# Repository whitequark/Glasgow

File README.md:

# Glasgow Debug Tool

**Want one? The [Crowdsupply campaign](https://www.crowdsupply.com/1bitsquared/glasgow) is now live.**

**Let's chat! Our IRC channel is [#glasgow at libera.chat](irc://irc.libera.chat/glasgow); our Discord channel is [#glasgow at 1BitSquared's Discord server](https://1bitsquared.com/pages/chat).**

**Important note: if you are looking to assemble boards yourself, use only revC1.**

## What is Glasgow?

Glasgow is a tool for exploring digital interfaces, aimed at embedded developers, reverse engineers, digital archivists, electronics hobbyists, and everyone else who wants to communicate to a wide selection of digital devices with high reliability and minimum hassle. It can be attached to most devices without additional active or passive components, and includes extensive protection from unexpected conditions and operator error.

The Glasgow hardware can support many digital interfaces because it uses reconfigurable logic. Instead of only offering a small selection of standard hardware supported interfaces, it uses an FPGA to adapt on the fly to the task at hand without compromising on performance or reliability, even for unusual, custom or obsolete interfaces.

The Glasgow software is a set of building blocks designed to eliminate incidental complexity. Each interface is packaged into a self-contained *applet* that can be used directly from the command line, or reused as a part of a more complex system. Using Glasgow does not require any programming knowledge, although it becomes much more powerful if you know a bit of Python.

## What can I do with Glasgow?

Some of the tasks Glasgow can do well are:

  * communicate via UART,
    * automatically determine and follow the baud rate of device under test,
  * initiate transactions via SPI or I²C,
  * read and write 24-series I²C EEPROMs,
  * read and write 25-series SPI Flash memories,
    * determine memory parameters via SFDP,
  * read and write ONFI-compatible Flash memories,
    * determine memory parameters via ONFI parameter page,
  * read and write parallel 27/28/29-series EPROMs, EEPROMs and Flash memories,
    * determine the extent of floating gate charge decay and rescue data,
  * program and verify AVR microcontrollers with SPI interface,
  * automatically determine unknown JTAG pinout,
  * play back JTAG SVF files,
  * debug ARC processors via JTAG,
  * debug some MIPS processors via EJTAG,
  * program and verify XC9500XL CPLDs via JTAG,
  * communicate using nRF24L01(+) radios,
  * program nRF24LE1 and nRF24LU1(+) microcontrollers,
  * synthesize sound using a Yamaha OPLx/OPM chip and play it in real time on a webpage,
  * read raw modulated data from 5.25"/3.5" floppy drives,
  * ... and more!

Everything above can be done with only a Glasgow revC board, some wires, and depending on the device under test, external power.

## How does using Glasgow look like?

Watch a typical command-line workflow in this screencast:

## What hardware does Glasgow use?

The Glasgow hardware evolves over time, with each major milestone called a "revision". Although all revisions are, and will always be supported with the same software, they vary significantly in their capabilities, and the chosen revision will limit the possible tasks.

Glasgow boards use a version in the `revXN` format, where `X` is a revision letter (increased on major design changes) and `N` is a stepping number (increased on any layout or component changes). For example, `revC0` is the first stepping of revision C.

### revA/revB

Revisions A and B have not been produced in significant amounts, contain major design issues, and are therefore mostly of historical interest. Nevertheless, everyone who has one of the revA/revB boards can keep using them—forever.

### revC

Revision C is the latest revision and is being prepared for mass production. It provides 16 I/O pins with a data rate up to approx. 100 Mbps/pin (50 MHz)\*, independent direction control and independent programmable pull-up/pull-down resistors. The I/O pins are grouped into two I/O ports, each of which can use any voltage from 1.8 V to 5 V, sense and monitor I/O voltage of the device under test, as well as provide up to 150 mA of power. The board uses USB 2 for power, configuration, and communication, achieving up to 336 Mbps (42 MB/s) of sustained combined throughput.

<sub>\* Data rate achievable in practice depends on many factors and will vary greatly with specific interface and applet design. 12 Mbps/pin (6 MHz) can be achieved with minimal development effort; reaching higher data rates requires careful HDL coding and a good understanding of timing analysis.</sub>

## What software does Glasgow use?

Glasgow is written entirely in Python 3. The interface logic that runs on the FPGA is described using [nMigen](https://github.com/nmigen/nmigen/), which is a Python-based domain specific language. The supporting code that runs on the host PC is written in Python with [asyncio](https://docs.python.org/3/library/asyncio.html). This way, the logic on the FPGA can be assembled on demand for any requested configuration, keeping it as fast and compact as possible, and code can be shared between gateware and software, removing the need to add error-prone "glue" boilerplate.

Glasgow would not be possible without the [open-source iCE40 FPGA toolchain](http://www.clifford.at/icestorm/), which is not only very reliable but also extremely fast. It is so fast that FPGA bitstreams are not cached (beyond not rebuilding the bitstream already on the device), as it only takes a few seconds to build one from scratch for something like an UART. When developing a new applet it is rarely necessary to wait for the toolchain.

Implementing reliable, high-performance USB communication is not trivial—packetization, buffering, and USB quirks add up. Glasgow abstracts away USB: on the FPGA, the applet gateware writes to or reads from a FIFO, and on the host, applet software writes to or reads from a socket-like interface. Idiomatic Python code can communicate at maximum USB 2 bulk bandwidth on a modern PC without additional effort. Moreover, when a future Glasgow revision will use Ethernet in addition to USB, no changes to applet code will be required.

Debugging new applets can be hard, especially if bidirectional buses are involved. Glasgow provides a built-in cycle-accurate logic analyzer that can relate the I/O pin level and direction changes to commands and responses received and sent by the applet. The logic analyzer compresses waveforms and can pause the applet if its buffer is about to overflow.

## How do I set up Glasgow?

**If these instructions don't work for you, please [file it as a bug](https://github.com/GlasgowEmbedded/glasgow/issues), so that the experience can be made more smooth for everyone.**

### ... with Linux?

You will need git and Python 3.7 (or a newer version, in which case replace `3.7` with that version below). On a Debian or Ubuntu system these can be installed with:

    apt-get install --no-install-recommends git python3.7 python3-setuptools \
      python3-libusb1 python3-aiohttp python3-bitarray python3-crcmod

You will also need Yosys and nextpnr-ice40, both from the master branch. Follow the setup instructions for [Yosys](https://github.com/yosysHQ/yosys/#setup) and [nextpnr](https://github.com/YosysHQ/nextpnr/#nextpnr-ice40).

Obtain the source code:

    git clone https://github.com/GlasgowEmbedded/glasgow
    cd glasgow

Configure your system to allow unprivileged access (for anyone in the `plugdev` group) to the Glasgow hardware:

    sudo cp config/99-glasgow.rules /etc/udev/rules.d

Install the dependencies and the scripts for the current user:

    cd software
    python3.7 setup.py develop --user

The scripts are placed in `$HOME/.local/bin`, so be sure to add that directory to the `PATH` environment variable; after this, you can run `glasgow` from a terminal. Instead of adjusting `PATH` it is also possible to use `python3.7 -m glasgow.cli`.

To update the source code, do:

    cd glasgow
    git pull

### ... with macOS?

If you haven't already, install [Homebrew](https://brew.sh/). Now:

    brew install python
    brew tap ktemkin/oss-fpga
    brew install --HEAD icestorm yosys nextpnr-ice40

Obtain the source code:

    git clone https://github.com/GlasgowEmbedded/glasgow
    cd glasgow

Install the dependencies and the scripts for the current user:

    cd software
    python3 setup.py develop

The scripts will be installed in `/usr/local/bin`, which should already be in your `PATH`.

### ... with Windows?

Although first-class Windows support is an important goal and Glasgow already works on Windows, the installation process is not yet ready.

## How do I use Glasgow?

*Note:* if you've just assembled a new board, you'll need to follow the [factory flashing](./docs/internals_flashing.rst) instructions first.

Once you've installed the Glasgow CLI, we can run a few commands to check that it's working. First, plug in your board and check if the CLI can talk to it:

    glasgow voltage

This should display the configured and sensed voltages on Glasgow's IO ports.

Next, we can try running an applet. Here, we'll use the [uart](./software/glasgow/applet/interface/uart) applet to create a 3.3V serial port on pins 0 and 1:

    glasgow run uart -V3.3 tty

If you receive any errors when running this command, it means your FPGA toolchain (yosys/nextpnr) is not working. If it is working, you should see:

    I: g.applet.interface.uart: running on a TTY; enter `Ctrl+\ q` to quit

You'll also see the `VIO` LEDs light up on your Glasgow board to indicate there is now voltage present on the ports.

If your serial port isn't connected to anything, you'll also see some harmless `frame or parity errors detected` warnings. As the message says, you'll need to use `Ctrl+\ q` to exit the applet.

If all this succeeded, your Glasgow is working!

## Who made Glasgow?

  * [@whitequark](https://github.com/whitequark) came up with the design, coordinates the project and implements most of gateware and software;
  * [@awygle](https://github.com/awygle) designed the power/analog port circuitry and helped with layout of revB;
  * [@marcan](https://github.com/marcan) improved almost every aspect of hardware for revC;
  * [@esden](https://github.com/esden) is handling batch manufacturing;
  * [@smunaut](https://github.com/smunaut) provided advice crucial for stability and performance of USB communication;
  * [@electronic_eel](https://github.com/electronic_eel) improved the hardware for revC2, designed the test jig and is working on advanced protection circuitry;
  * [@Attie](https://github.com/attie) improved and refactored many applets;
  * ... and many [other people](https://github.com/GlasgowEmbedded/Glasgow/graphs/contributors).

## License

Glasgow is distributed under the terms of both 0-clause BSD license as well as Apache 2.0 license.

See [LICENSE-0BSD](LICENSE-0BSD.txt) and [LICENSE-Apache-2.0.txt](LICENSE-Apache-2.0.txt) for details.

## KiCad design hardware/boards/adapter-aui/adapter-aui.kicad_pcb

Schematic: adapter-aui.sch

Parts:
C1, C2, C9: 1u; C_0603_1608Metric_Pad1.05x0.95mm_HandSolder
C3, C4: 100n; C_0603_1608Metric_Pad1.05x0.95mm_HandSolder
C5, C6, C7: 10u; C_0603_1608Metric_Pad1.05x0.95mm_HandSolder
C8: DNP; C_0603_1608Metric_Pad1.05x0.95mm_HandSolder
D1, D2: MBR0520; D_SOD-123
J1, J2: Conn_02x10_Odd_Even; IDC-Header_2x10_P2.54mm_Vertical
J3: DB15_Female_MountingHoles; DSUB-15_Female_Horizontal_P2.77x2.84mm_EdgePinOffset9.90mm_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
J4: DC5521; BarrelJack_Horizontal
JP1: SolderJumper_3_Open; SolderJumper-3_P1.3mm_Open_RoundedPad1.0x1.5mm
L1: 22u; L_7.3x7.3_H4.5
R1, R2, R4, R5, R6, R7, R9, R10: 12; R_0603_1608Metric_Pad1.05x0.95mm_HandSolder
R3, R8: 115; R_0603_1608Metric_Pad1.05x0.95mm_HandSolder
R11: 1.5M; R_0603_1608Metric_Pad1.05x0.95mm_HandSolder
R12: 174k; R_0603_1608Metric_Pad1.05x0.95mm_HandSolder
R13, R14: 78; R_0603_1608Metric_Pad1.05x0.95mm_HandSolder
TP1, TP2, TP3, TP4, TP5, TP6, TP7, TP8, TP9, TP10, TP11, TP12, TP13: TestPoint; TestPoint_THTPad_1.5x1.5mm_Drill0.7mm
U1, U2: ADM3490E; SOIC-8_3.9x4.9mm_P1.27mm
U3: LD1117S33TR; SOT-223-3_TabPin2
U4: TPS61040DBV; SOT-23-5

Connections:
+3V3: C1.1, C2.1, C3.1, C4.1, C5.1, U1.1 (VCC), U2.1 (VCC), U3.2
+5V: C6.1, C7.1, J1.2, J2.2, JP1.3 (B), L1.1, U3.3, U4.5
/CI-A: J3.2, R14.2, TP5.1, U2.8 (A)
/CI-B: J3.9, R14.1, TP6.1, U2.7 (B)
/CO-A: J3.7, R9.1, TP7.1
/CO-B: J3.15, R6.1, TP8.1
/DI-A: J3.5, R13.2, TP1.1, U1.8 (A)
/DI-B: J3.12, R13.1, TP2.1, U1.7 (B)
/DO-A: J3.3, R4.1, TP3.1
/DO-B: J3.10, R1.1, TP4.1
/VP: C8.1, C9.1, D1.1 (K), D2.1 (K), J3.13, R11.1, TP9.1
/X-CI: J1.17, J2.9
/X-CO: J1.15, J2.7
/X-DI: J1.13, J2.5
/X-DO: J1.11, J2.3
/Y-CI: J1.9, TP13.1, U2.2 (RO)
/Y-CO: J1.7, TP12.1, U2.3 (DI)
/Y-DI: J1.5, TP11.1, U1.2 (RO)
/Y-DO: J1.3, TP10.1, U1.3 (DI)
GND: C1.2, C2.2, C3.2, C4.2, C5.2, C6.2, C7.2, C9.2, J1.4, J1.6, J1.8, J1.10, J1.12, J1.14, J1.16, J1.18, J2.4, J2.6, J2.8, J2.10, J2.12, J2.14, J2.16, J2.18, J3.0 (PAD), J3.1, J3.4, J3.6, J3.8, J3.11 (P111), J3.14, J4.2, JP1.1 (A), R12.2, U1.4 (GND), U2.4 (GND), U3.1, U4.2
unnamed: C8.2, R11.2, R12.1, U4.3
unnamed: D1.2 (A), L1.2, U4.1
unnamed: D2.2 (A), J4.1
unnamed: JP1.2 (C), U4.4
unnamed: R1.2, R2.1, R3.2
unnamed: R2.2, U1.6 (Z)
unnamed: R3.1, R4.2, R5.1
unnamed: R5.2, U1.5 (Y)
unnamed: R6.2, R7.1, R8.2
unnamed: R7.2, U2.6 (Z)
unnamed: R8.1, R9.2, R10.1
unnamed: R10.2, U2.5 (Y)

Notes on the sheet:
IDC-20 connector to Glasgow
IDC-20 connector to next daisy-chained adapter
OFF
There are no cheap or easily available AUI transceivers anymore. Because of this, we construct an AUI transceiver using cheap RS-422/485 drivers. This causes this device to deviate from 802.3 Clause 7 as follows: 1. 802.3 requires indefinite protection from a ±16 V fault. This device provide indefi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
AUI connector to MAU, or, AUI connector to DTE, if crossover cable is used
802.3 requires 1 V differential swing, but RS-422 drivers like ADM3490E are rail-to-rail (3.3 V in this circuit), requiring an H-pad matching network.

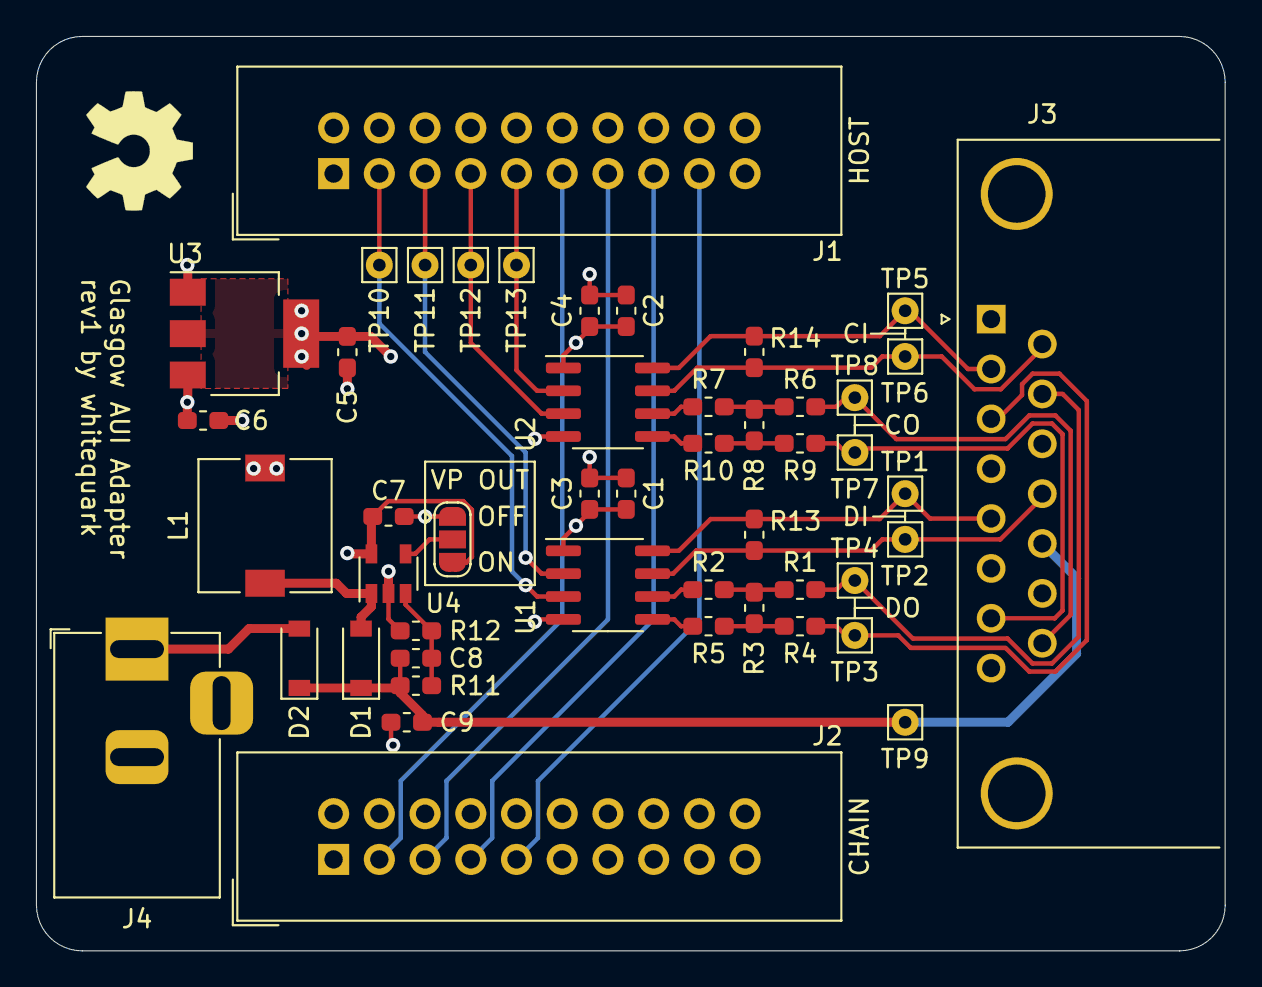
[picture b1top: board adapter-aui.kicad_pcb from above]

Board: 4 copper layers, 66.0 x 50.8 mm, 48 parts (0 on the bottom side), 32 nets.

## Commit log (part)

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2019-05-03 applet.program.pic.lv: WIP
2019-07-31 applet.sensor.keyboard_ps2: new applet (WIP)
2019-11-10 (WIP) Add an alternative setting using interrupt endpoints.
    To improve worst-case latency while still keeping guaranteed
    delivery.
2020-01-19 WIP Ethernet AUI adapter.
2020-10-26 applet.debug.msp430.sbw: new applet.
2020-10-27 [WIP] reorganize the applet
2020-11-17 [WIP] arch.arm.mem_ap: add MEM-AP register definitions.
2020-12-03 applet.sensor.scd30: add a note about starting the sensor first
2020-12-03 applet.sensor.scd30: add a note about the startup delay
2023-10-20 access.direct.arguments: indicate when pin(s) are required.
2023-10-21 applet.interface.gpib_controller: new applet.
2023-10-23 applet.program.avr.jtag: new applet. (WIP)
2023-10-29 applet.radio.sx1276: new applet. (WIP)
2024-07-18 gateware.stream.{Queue,AsyncQueue}: new component.
2024-07-18 platform.generic: delegate `GlasgowPlatformPort.direction` to `.io_port`.
    This doesn't actually change behavior at the moment, but would be
    the correct implementation if we ever narrow underlying port directions.
2024-07-18 gateware.qspi.QSPIController: new component.
    This component is a fully pipelined, zero wait states SPI, dual-SPI,
    and quad-SPI controller designed for high performance memory device
    access.
2024-07-18 gateware.ports: add `SimulationPort` and `SimulationPlatform`.
    The `SimulationPort` class is an implementation of the proposed RFC #69
    (amaranth-lang/amaranth#1417, amaranth-lang/rfcs#69).
    The `SimulationPlatform` class is a temporary workaround for the lack
    of built-in knowledge of `SimulationPort` by `io.{Buffer,FFBuffer}`.
    In conjunction with the `PortGroup` class, these classes enable testing
    I/O gateware. Eventually they should be integrated with the Glasgow
2024-07-18 gateware.iostream.IOStream: new component.
    This component is a reusable I/O buffer to stream adapter, suitable for
    interfaces where the clock is generated internally on the FPGA.
2024-07-18 [WIP] applet.interface.qspi_controller: new applet.
2024-07-18 repro
2024-07-18 more repro
2024-07-29 applet.memory.25x: use QSPI controller instead of SPI.
    This makes it possible to use higher transfer rates, at the cost of
    WP# and HOLD# pins becoming mandatory.
2024-11-08 Deploying to gh-pages from @ whitequark/glasgow@b3eb5c7cb9fd823f2cd505247c5cc72fac257a33 🚀
2024-12-17 software: update to Amaranth 0.5.4.
2024-12-17 Deploying to gh-pages from @ whitequark/glasgow@6dfb5dbb13d257f0d4412dc868a6ffadfa0abc69 🚀
2025-06-03 gateware.stream: add `PacketQueue`.
2025-06-14 gateware.iostream: expose domain parameters on `StreamIOBuffer`.
2025-06-14 gateware.stream: add `PacketExtender`.
2025-06-14 gateware.ethernet: add Ethernet controller.
2025-06-14 applet.interface.ethernet.rgmii: new applet.
2025-06-15 applet.interface.ethernet.rmii: new applet.
2025-07-04 applet.program.nrf24lx1: migrate to V2 API.
2025-07-06 applet.radio.nrf24l01: migrate to V2 API.
2025-08-05 abstract: fix typo. NFC
2025-08-05 software: explicitly `return None` if result is optional (ruff RET502).
2025-08-05 software: fix `None` comparison (ruff E711). NFC
2025-08-05 software: keep strong references to asyncio tasks (ruff RUF006). NFCI
2025-08-05 software: mark unused unpacked variables (ruff unsafe RUF059). NFC
2025-08-05 protocol.jesd3: raise `TypeError` instead of `ValueError`.
2025-08-05 software: fix use of undocumented `logging.WARN` (ruff LOG009). NFC
2025-08-05 software: fix use of dummy variables (ruff RUF052). NFC
2025-08-05 software: explicitly return on all paths (ruff unsafe RET503). NFCI
2025-08-05 software: fix comprehension syntax (ruff unsafe C4). NFCI
2025-08-05 software: capture induction variable in closures (ruff B023). NFCI
2025-08-05 software: rename unused loop control vars (ruff unsafe B007). NFCI
2025-08-05 software: fix invalid `.format()` calls (ruff F523).
2025-08-05 software: annotate attr access for side effect (ruff B018). NFC
2025-08-05 software: fix undefined names (ruff F821).
2025-08-05 software: avoid useless `return` (ruff safe PLR1711). NFC
2025-08-05 software: use f-string type conversions (ruff safe RUF010). NFC
2025-08-05 software: avoid implicit `Optional` (ruff RUF013).
2025-08-05 software: avoid bare `except:` (ruff E722).
2025-08-05 software: remove trailing comma on empty tuple (ruff COM818). NFC
    [skip blame]
2025-08-05 software: use `is` for type comparisons (ruff E721). NFCI
2025-08-05 software: use proper dict iterators (ruff safe PERF102). NFC
2025-08-05 software: avoid quadratic list summation (ruff RUF017). NFCI
2025-08-05 software: avoid raising `Exception` (ruff TRY002).
2025-08-05 software: parenthesize `and`/`or` expressions (ruff safe RUF021). NFC
2025-08-05 software: avoid unnecessary dict lookup (ruff safe PLR1733). NFC
2025-08-05 software: use `try`-`else` where appropriate (ruff TRY300). NFCI
2025-08-05 software: fix docstring formatting (ruff D400,D404). NFC
    [skip blame]
2025-08-05 software: normalize to use double quotes (ruff safe Q). NFC
    [skip blame]
2025-08-05 software: fix line length (ruff E501). NFCI
2025-08-05 software: fix whitespace (ruff safe E*,W*). NFC
    [skip blame]
    ```
    [lint]
    preview = true
    select = [
    "E262", # no-space-after-inline-comment
2025-08-05 software: fix docstring formatting (ruff safe D*). NFC
    [skip blame]
    ```
    [lint]
    preview = true
    select = [
    "D200", # unnecessary-multiline-docstring
2025-08-05 software: fix non-multiple-of-4 indentation (ruff E111). NFC
2025-08-05 software: remove unused imports (ruff safe F401). NFC
2025-08-05 software: remove unused imports (ruff unsafe F401). NFC
2025-08-05 software: upgrade syntax (ruff unsafe UP,!UP031). NFCI
2025-08-05 software: upgrade formatting syntax (ruff unsafe UP031, flynt). NFCI
    The "aggressive" mode of flynt appears to corrupt format strings with
    precision: instead of converting to `{foo:{bar}d}`, it converts to
    `{foo:{{}}d}`. This was fixed manually.
2025-08-05 software: use Ruff and pre-commit.ci to keep it tidy.
2025-08-05 manual: explain how pre-commit.ci works.
2025-08-10 Deploying to gh-pages from @ whitequark/glasgow@fe3fd4400155285934113357e04e6a3e938b450c 🚀
